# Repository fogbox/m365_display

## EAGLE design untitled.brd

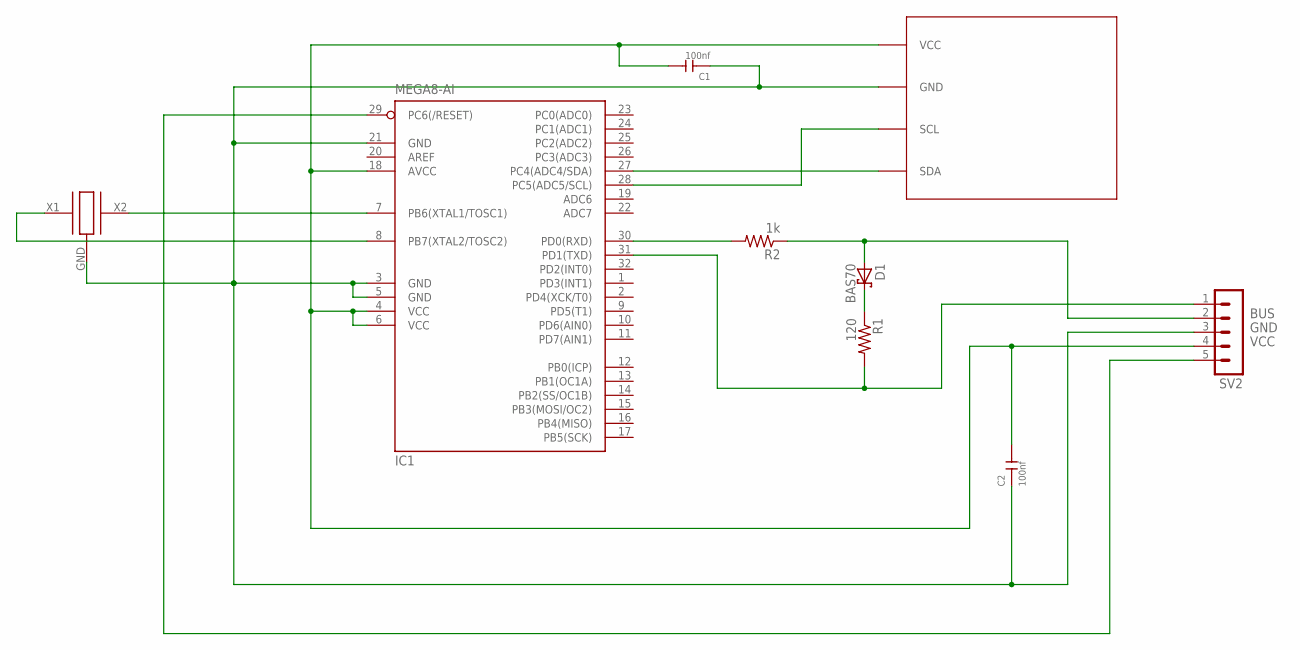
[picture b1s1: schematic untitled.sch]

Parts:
C1, C2: 100nf; C0805
D1: BAS70; SOT23
IC1: MEGA8-AI; TQFP32-08
R1: 120; M0805
R2: 1k; M0805
SV2: MA05-1
U$1: AMOLED_ADAFRUIT; AMOLED_PCB
U$2: MURATA_XTALL; MURATA

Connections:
BUS: D1.1 (A), R2.1, SV2.2
GND: C1.1, C2.1, IC1.3 (GND), IC1.5 (GND), IC1.21 (GND), SV2.3, U$1.GND, U$2.GND
unnamed: D1.3 (C), R1.1
unnamed: IC1.7 (PB6(XTAL1/TOSC1)), U$2.X2
unnamed: IC1.8 (PB7(XTAL2/TOSC2)), U$2.X1
unnamed: IC1.30 (PD0(RXD)), R2.2
unnamed: IC1.29 (PC6(/RESET)), SV2.5
SCL: IC1.28 (PC5(ADC5/SCL)), U$1.SCL
SDA: IC1.27 (PC4(ADC4/SDA)), U$1.SDA
TX: IC1.31 (PD1(TXD)), R1.2, SV2.1
VCC: C1.2, C2.2, IC1.4 (VCC), IC1.6 (VCC), IC1.18 (AVCC), SV2.4, U$1.VCC

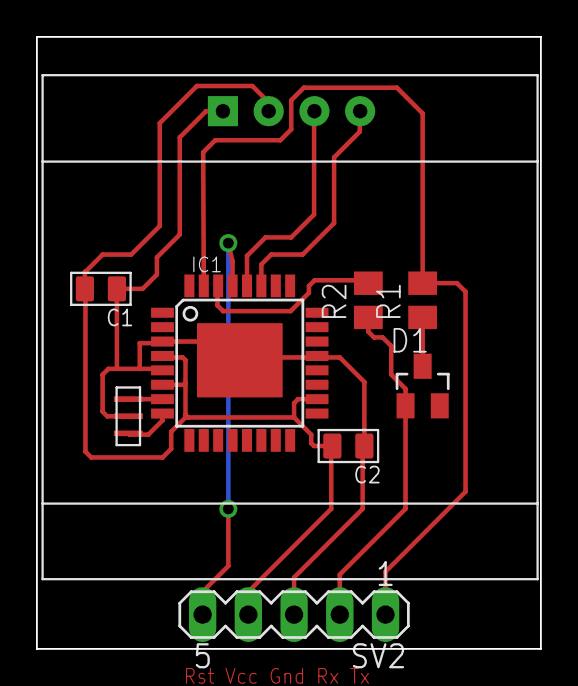
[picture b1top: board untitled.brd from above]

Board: 2 copper layers, 28.0 x 34.0 mm, 9 parts (0 on the bottom side), 11 nets.

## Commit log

2018-05-15 comment
2018-05-15 # Changes to be committed:
2018-05-15 comment 1#
2018-05-15 another coment#
2018-05-15 another comment#
2018-05-16 comment#
2018-05-16 shit happends
2018-05-17 ksjdkjks #
2018-05-17 subtotal :)
2018-05-17 small update
2018-05-17 subtototal
2018-05-17 subtotal*2
2018-05-18 simple commit comment
2018-05-27 add silent mode
2018-06-07 add menu
2018-06-08 FIX BUG WITH BRAKE & THROTTLE
2018-06-08 bugfix, perfomance counter
2018-06-08 _____
2018-06-08 fix warnings
2018-06-15 some changes.
2018-07-08 Add files via upload
    img2
2018-07-08 Add files via upload
    Eagle files
2019-05-27 u8g2
2019-08-05 bugfix
2019-08-05 bug fixes
